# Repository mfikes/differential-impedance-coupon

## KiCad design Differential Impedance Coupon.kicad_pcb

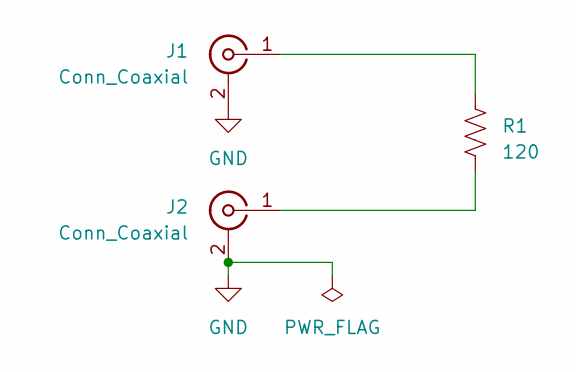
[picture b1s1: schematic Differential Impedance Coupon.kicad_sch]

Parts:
J1, J2: Conn_Coaxial; SMA_142_0701_851_EdgeMount
R1: 120; R_0805_2012Metric

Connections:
GND: J1.2 (Ext), J2.2 (Ext)
unnamed: J1.1 (In), R1.1
unnamed: J2.1 (In), R1.2

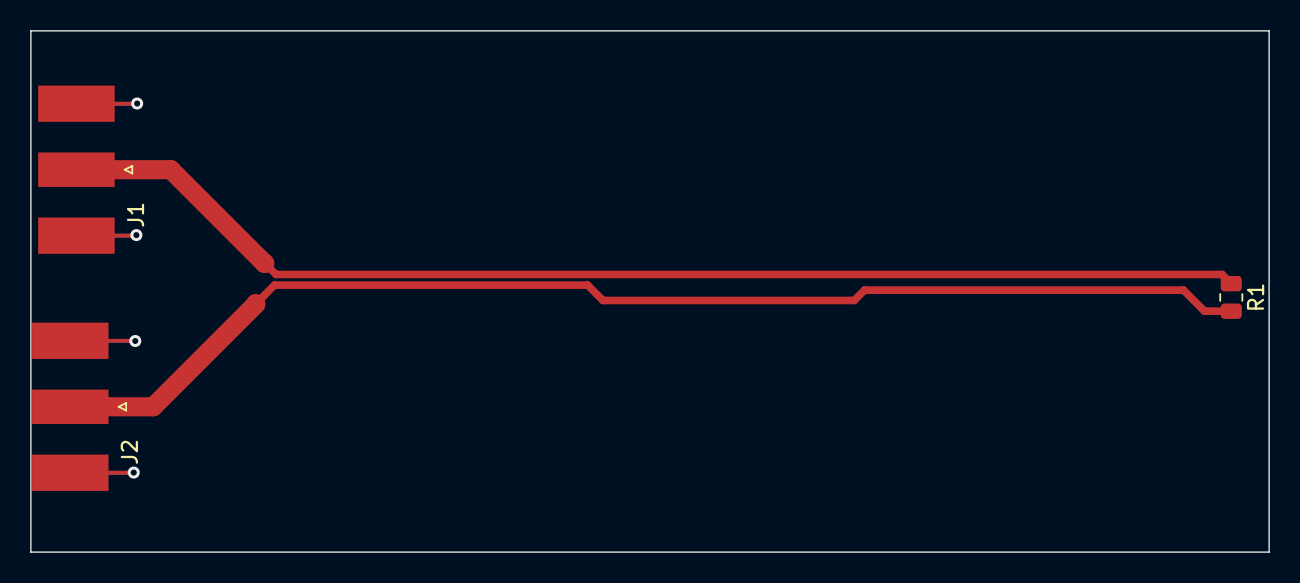
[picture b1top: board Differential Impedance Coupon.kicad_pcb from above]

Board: 2 copper layers, 82.2 x 34.6 mm, 3 parts (0 on the bottom side), 3 nets.

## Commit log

2023-03-13 Initial schematic, add edge launch model
2023-03-13 wrong footprint
2023-03-13 Add SMA connector footprint
2023-03-13 Hook up footprint
2023-03-13 Footprint for resistor
2023-03-13 Lay out some of the traces
